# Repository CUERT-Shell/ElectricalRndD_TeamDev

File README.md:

# Electrical_RndD_Team

R&D Team Frequent work space

Continous R&D Development for Submodule , Modules and similar 

For continous Dev Each member Creates a branch or works on the branch created for them , and ask merge requests or similar at each milestone

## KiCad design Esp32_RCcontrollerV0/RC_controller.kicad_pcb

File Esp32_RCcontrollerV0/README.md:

# RC NodeMcu 32s shield

* Onboard Buck Converter (12V--->5V)
* Reverse Connection protection for the 12V input 
* 8x 5V digital outputs (Level Shifted from 3.3V using BOB-12009 or similar) screw terminated
* 2x Dac outputs (IO25, IO26) screw terminated
* 4x ADC inputs   (IO35, IO34, IO39, IO36) screw terminated
* 3x 5V screw terminal (Outputs)
* I2C , Uart0 Headers

#### Warning
Never Connect usb to the esp32, while plugging in the 12V input (At least remove the buck enable header)

production : gerbers for production and bom  
bom : html interactive bom  
LIB : component library used  
Doc : 3d model , images , schematic (pdf) , etc  s

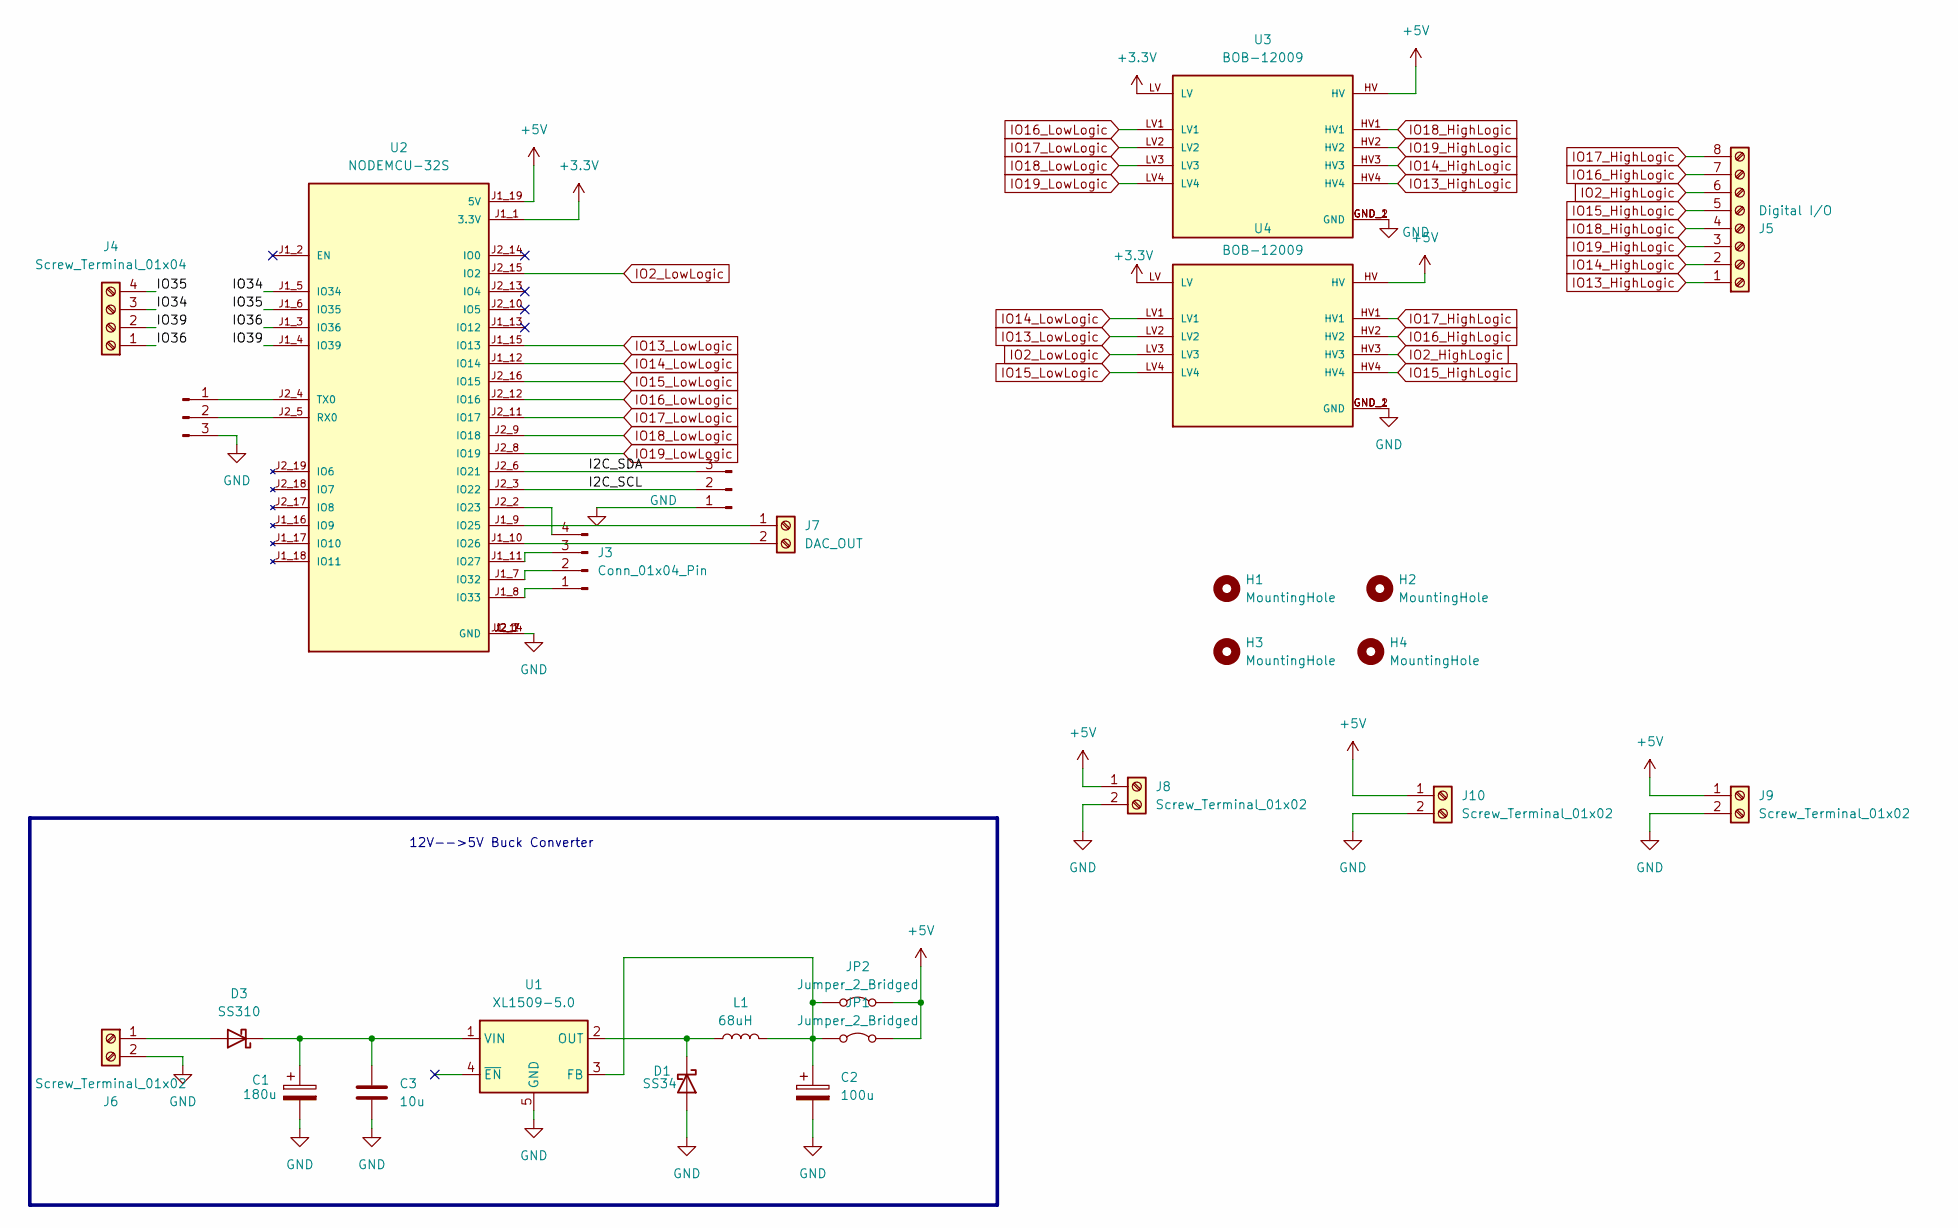
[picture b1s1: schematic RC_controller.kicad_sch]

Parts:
C1: 180u; CP_Radial_D7.5mm_P2.50mm
C2: 100u; CP_Radial_D7.5mm_P2.50mm
C3: 10u; C_1206_3216Metric_Pad1.33x1.80mm_HandSolder
D1: SS34; D_SMA
D3: SS310; D_SMA
H1, H2, H3, H4: MountingHole; MountingHole_3.2mm_M3
J1, J2: Conn_01x03_Pin; PinHeader_1x03_P2.54mm_Vertical
J3: Conn_01x04_Pin; PinHeader_1x04_P2.54mm_Vertical
J4: Screw_Terminal_01x04; TerminalBlock_Phoenix_PT-1,5-4-3.5-H_1x04_P3.50mm_Horizontal
J5: Digital I/O; TerminalBlock_Phoenix_PT-1,5-8-3.5-H_1x08_P3.50mm_Horizontal
J6, J8, J9, J10: Screw_Terminal_01x02; TerminalBlock_Phoenix_PT-1,5-2-3.5-H_1x02_P3.50mm_Horizontal
J7: DAC_OUT; TerminalBlock_Phoenix_PT-1,5-2-3.5-H_1x02_P3.50mm_Horizontal
JP1, JP2: Jumper_2_Bridged; PinHeader_1x02_P2.54mm_Vertical
L1: 68uH; IND-SMD_L7.1-W6.6_H5.0
U1: XL1509-5.0; SOIC-8_3.9x4.9mm_P1.27mm
U2: NODEMCU-32S; MODULE_NODEMCU-32S; PARTREV V1
U3, U4: BOB-12009; CONV_BOB-12009; PARTREV 01

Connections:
+3.3V: U2.J1_1 (3.3V), U3.LV, U4.LV
+5V: J8.1, J9.1, J10.1, JP1.2 (B), JP2.2 (B), U2.J1_19 (5V), U3.HV, U4.HV
/I2C_SCL: J2.2, U2.J2_3 (IO22)
/I2C_SDA: J2.3, U2.J2_6 (IO21)
/IO34: J4.3, U2.J1_5 (IO34)
/IO35: J4.4, U2.J1_6 (IO35)
/IO36: J4.1, U2.J1_3 (IO36)
/IO39: J4.2, U2.J1_4 (IO39)
GND: C1.2, C2.2, C3.2, D1.2 (A), J1.3, J2.1, J6.2, J8.2, J9.2, J10.2, U1.5 (GND), U1.6 (GND), U1.7 (GND), U1.8 (GND), U2.J1_14 (GND), U2.J2_1 (GND), U2.J2_7 (GND), U3.GND_1 (GND), U3.GND_2 (GND), U4.GND_1 (GND), U4.GND_2 (GND)
IO2_HighLogic: J5.6, U4.HV3
IO2_LowLogic: U2.J2_15 (IO2), U4.LV3
IO13_HighLogic: J5.1, U3.HV4
IO13_LowLogic: U2.J1_15 (IO13), U4.LV2
IO14_HighLogic: J5.2, U3.HV3
IO14_LowLogic: U2.J1_12 (IO14), U4.LV1
IO15_HighLogic: J5.5, U4.HV4
IO15_LowLogic: U2.J2_16 (IO15), U4.LV4
IO16_HighLogic: J5.7, U4.HV2
IO16_LowLogic: U2.J2_12 (IO16), U3.LV1
IO17_HighLogic: J5.8, U4.HV1
IO17_LowLogic: U2.J2_11 (IO17), U3.LV2
IO18_HighLogic: J5.4, U3.HV1
IO18_LowLogic: U2.J2_9 (IO18), U3.LV3
IO19_HighLogic: J5.3, U3.HV2
IO19_LowLogic: U2.J2_8 (IO19), U3.LV4
unnamed: D1.1 (K), L1.1, U1.2 (OUT)
unnamed: D3.2 (A), J6.1
unnamed: C1.1, C3.1, D3.1 (K), U1.1 (VIN)
unnamed: J1.1, U2.J2_4 (TX0)
unnamed: J1.2, U2.J2_5 (RX0)
unnamed: J3.1, U2.J1_8 (IO33)
unnamed: J3.2, U2.J1_7 (IO32)
unnamed: J3.3, U2.J1_11 (IO27)
unnamed: J3.4, U2.J2_2 (IO23)
unnamed: J7.1, U2.J1_9 (IO25)
unnamed: J7.2, U2.J1_10 (IO26)
unnamed: C2.1, JP1.1 (A), JP2.1 (A), L1.2, U1.3 (FB)

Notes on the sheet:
12V-->5V Buck Converter

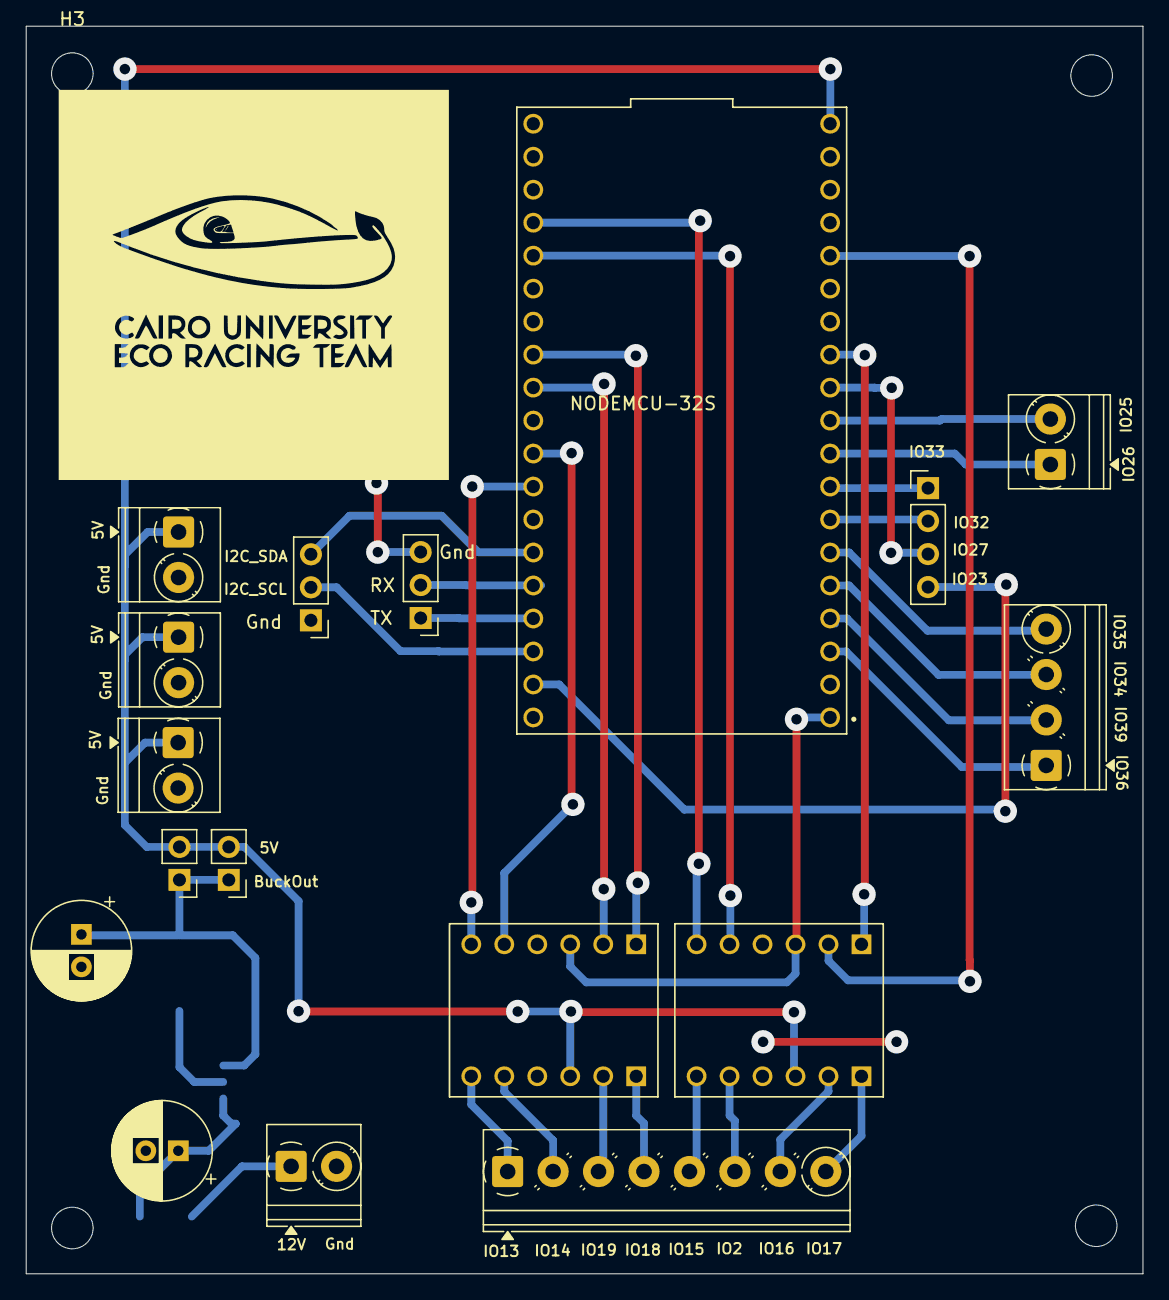
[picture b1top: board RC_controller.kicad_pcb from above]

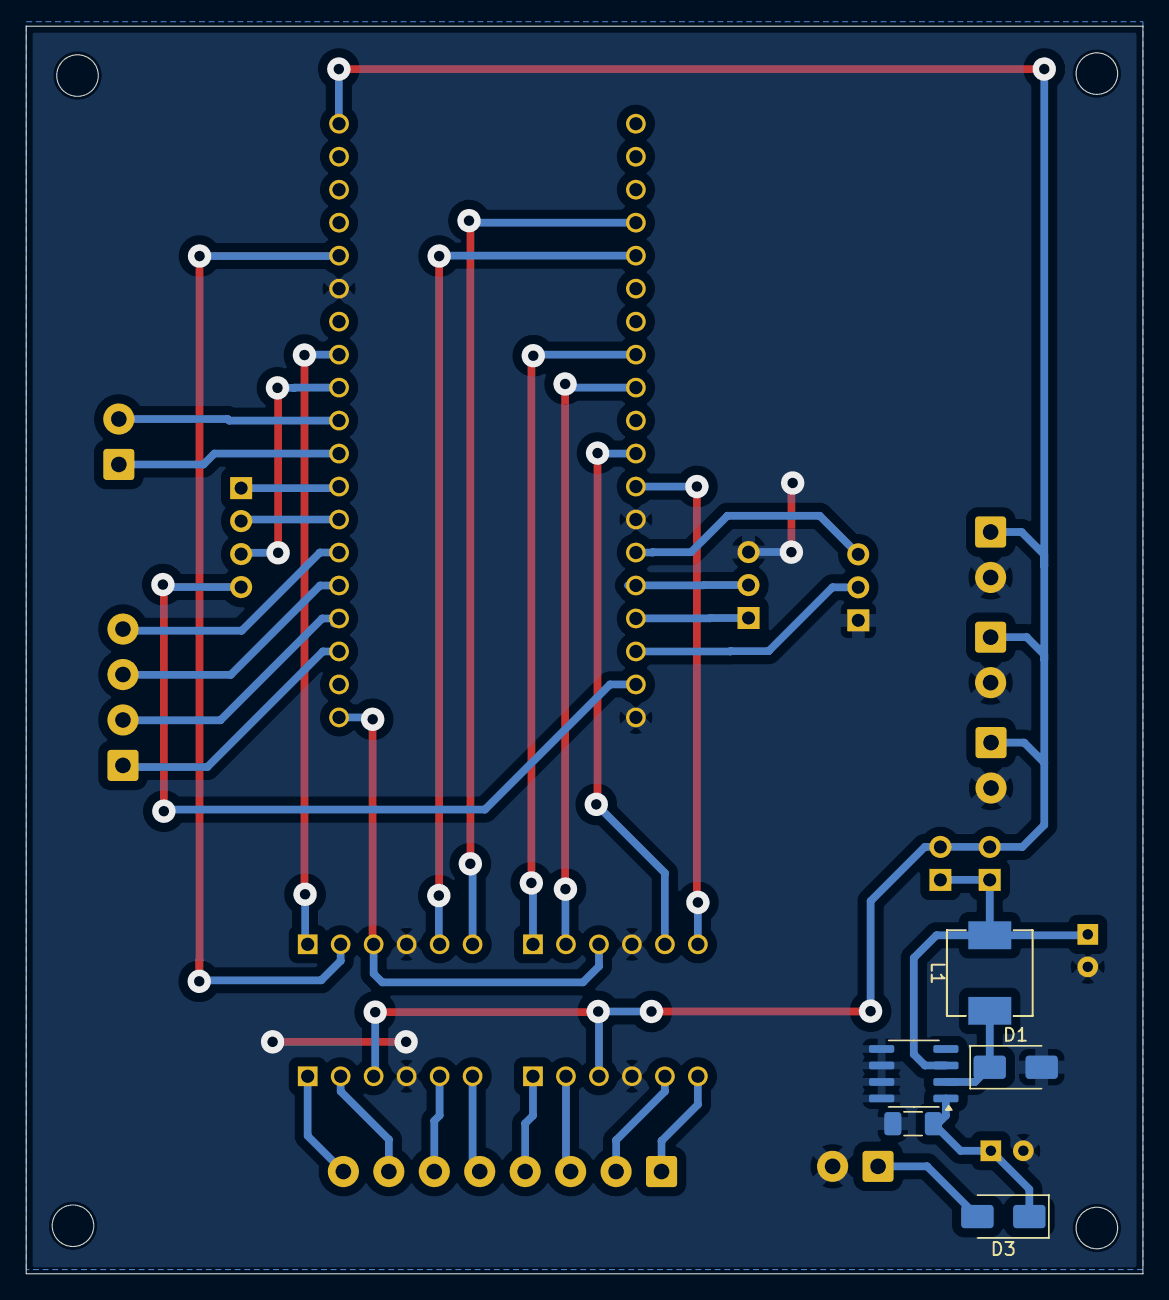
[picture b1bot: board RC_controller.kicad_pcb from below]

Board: 2 copper layers, 86.0 x 96.1 mm, 26 parts (5 on the bottom side), 37 nets.

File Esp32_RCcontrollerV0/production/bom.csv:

Designator,Footprint,Quantity,Value,LCSC Part #
C1,CP_Radial_D7.5mm_P2.50mm,1,180u,
C2,CP_Radial_D7.5mm_P2.50mm,1,100u,
C3,1206,1,10u,
D1,D_SMA,1,SS34,
D3,D_SMA,1,SS310,
"J1, J2",PinHeader_1x03_P2.54mm_Vertical,2,Conn_01x03_Pin,
"J10, J6, J8, J9","TerminalBlock_Phoenix_PT-1,5-2-3.5-H_1x02_P3.50mm_Horizontal",4,Screw_Terminal_01x02,
J3,PinHeader_1x04_P2.54mm_Vertical,1,Conn_01x04_Pin,
J4,"TerminalBlock_Phoenix_PT-1,5-4-3.5-H_1x04_P3.50mm_Horizontal",1,Screw_Terminal_01x04,
J5,"TerminalBlock_Phoenix_PT-1,5-8-3.5-H_1x08_P3.50mm_Horizontal",1,Digital I/O,
J7,"TerminalBlock_Phoenix_PT-1,5-2-3.5-H_1x02_P3.50mm_Horizontal",1,DAC_OUT,
"JP1, JP2",PinHeader_1x02_P2.54mm_Vertical,2,Jumper_2_Bridged,
L1,IND-SMD_L7.1-W6.6_H5.0,1,68uH,
U1,SOIC-8_3.9x4.9mm_P1.27mm,1,XL1509-5.0,
U2,MODULE_NODEMCU-32S,1,NODEMCU-32S,
"U3, U4",CONV_BOB-12009,2,BOB-12009,

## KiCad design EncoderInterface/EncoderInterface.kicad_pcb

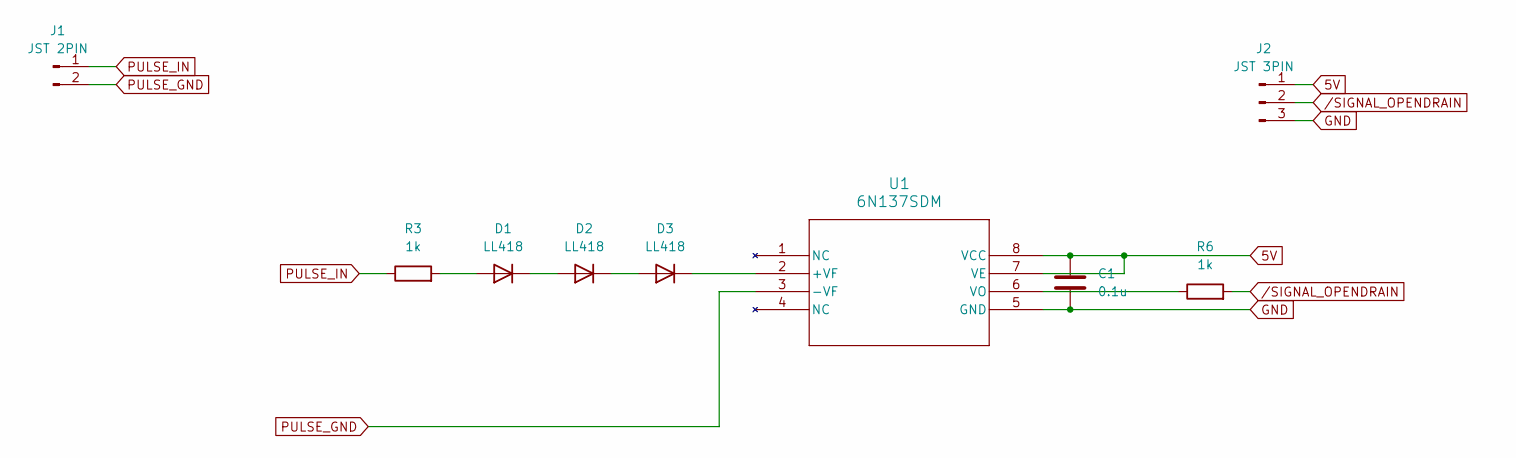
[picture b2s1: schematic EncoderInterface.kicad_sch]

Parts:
C1: 0.1u; C_1206_3216Metric_Pad1.33x1.80mm_HandSolder
D1, D2, D3: LL418; D_MiniMELF_Handsoldering
J1: JST 2PIN; JST_EH_B2B-EH-A_1x02_P2.50mm_Vertical
J2: JST 3PIN; JST_EH_B3B-EH-A_1x03_P2.50mm_Vertical
R3, R6: 1k; R_1206_3216Metric_Pad1.30x1.75mm_HandSolder
U1: 6N137SDM; SMT_6N137_OSI-M

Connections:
5V: C1.1, J2.1, U1.7 (VE), U1.8 (VCC)
GND: C1.2, J2.3, U1.5 (GND)
unnamed: D1.2 (A), R3.2
unnamed: D1.1 (K), D2.2 (A)
unnamed: D2.1 (K), D3.2 (A)
unnamed: D3.1 (K), U1.2 (+VF)
unnamed: R6.1, U1.6 (VO)
PULSE_GND: J1.2, U1.3 (-VF)
PULSE_IN: J1.1, R3.1
/SIGNAL_OPENDRAIN: J2.2, R6.2

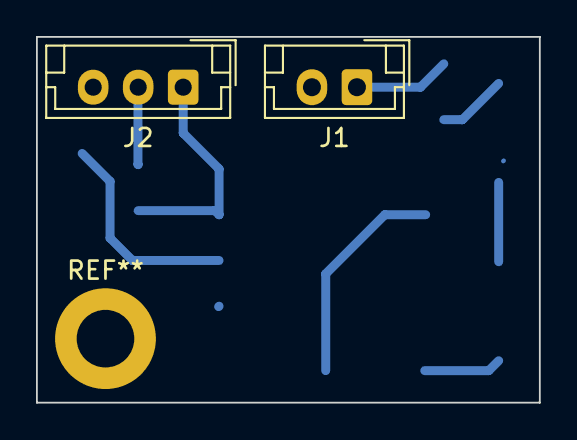
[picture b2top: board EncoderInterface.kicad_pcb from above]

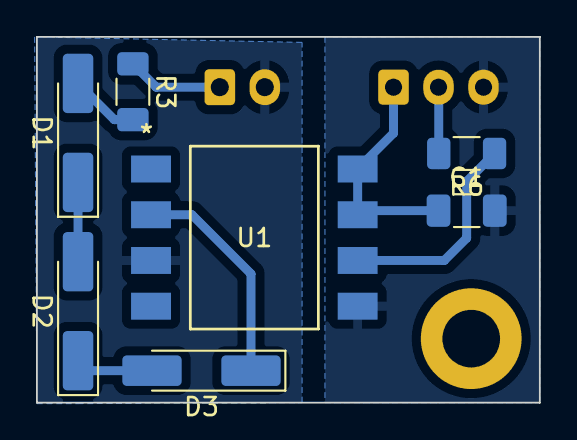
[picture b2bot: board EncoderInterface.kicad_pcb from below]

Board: 2 copper layers, 27.9 x 20.3 mm, 9 parts (7 on the bottom side), 10 nets.

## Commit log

2025-09-17 Motor driver controller PCB project
2025-09-17 Cuert RC controller V0.1
2025-09-19 Added Branching and Reorder
2025-09-22 Core updates
    Rework the board , Added Doc
